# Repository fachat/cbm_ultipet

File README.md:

# Ulti-PET

Note: this is a part of a larger set of repositories, with [upet_family](https://github.com/fachat/upet_family) as the main repository.

This is a re-incarnation of the Commodore PET computer(s) from the later 1970s.

It is build on a PCB that fits into a C64-II case (with extra cutouts for connectors), and has only parts that can still be obtained new in 2024/2025.
A 3D-printed case is also available specific for the Ulti-PET PCB.

Videos on the machine are coming soon on the [YouTube 8-bit times](https://youtube.com/playlist?list=PLi1dzy7kw1iybjcUccgjCV4fhNH4IPWSx) channel.

## Features

The board is built with a number of features:

- Commodore 3032 / 4032 / 8032 / 8296 with options menu to select at boot
  - Boot-menu to select different PET versions to run (BASIC 1, 2, 4)
  - 40 and 80 col character display
  - 8296 memory map emulation
  - IEEE488 interface (card edge and 24pin flat ribbon cable)
  - Tape connector (card edge, incl. 9V for proper tape operation)
  - PET graphics keyboard, or alternatively a C64 keyboard
- Improved system design:
  - 512k video RAM, plus 512k fast RAM, accessible using banks on the W65816 CPU
  - boot from an SPI Flash ROM
  - up to 13.5 MHz mode (via configuration register)
  - Write protection for the PET ROMs once copied to RAM
  - lower 32k RAM mappable from all of the 512k fast RAM
  - single 5V power supply (<1A) using USB-C connector
  - hardware and firmware support SD-Card and USB keyboard or mouse
- Improved Audio output:
  - Original beeper sound
  - Audio output using a DAC with DMA
  - Dual SID output
  - beeper, DAC, and SID are mixed into a stereo line output
  - integrated amplifier can drive <1W speakers
- Improved Video output:
  - VGA colour video output (222 RGB)
  - up to 96x72 characters on screen
  - hires modes up to a 720x576 resolution
  - Dual 16 out of 64 colour palette, Colour-PET or C128 VDC-compatible, Sprites
  - Hires graphics mode (using a configuration register)
  - modifyable character set
  - multiple video pages mappable to $8000 video mem address
- Extra I/O features:
  - Userport Joystick, software-switchable between single and dual joystick configs
  - fast serial IEC for Commodore's 1581 or 1571 disk drives (ROM support TBD)
  - 5V SPI interface for further extensions
  - 3.3V SPI interface for further extensions
  - Adafruit(tm) UEXT interface for further extensions (SPI shared with 3.3V SPI, includes I2C)
  - Dual UART serial, one RS232, one TTL (shared with UEXT, or the USB-C-to-serial)

## Overview

The system architecture is actually rather simple, as you can see in the following graphics.

The main functionality is "hidden" inside the FPGA. It does:

1. clock generation and management
2. memory mapping
3. video generation.
4. SPI interface and boot
5. DAC DMA

On the CPU side of the FPGA it is actually a rather almost normal 65816 computer, 
with the exception that the bank register (that catches and stores the address lines 
A16-23 from the CPU's data bus) is in the FPGA, and that there is no ROM. The ROM has been
replaced with some code in the FPGA that copies the initial program to the CPU accessible
RAM, taking it from the Flash Boot ROM via SPI. This actually simplifies the design,
as 

1. parallel ROMs are getting harder to come by and
2. they are typically not as fast as is needed, and
3. with the SPI boot they don't occupy valuable CPU address space.

The video generation is done using time-sharing access to the video RAM.
The VGA output is 720x576 at 50Hz, or 720x480 at 60 Hz. So there is a pixel clock of 27MHz.

The system runs at 13.5MHz, so a byte of pixel output (i.e. eight pixels) has four
memory accesses to VRAM. Two of them are reserved for video access, one for fetching the
character data (e.g. at $08xxx in the PET), and the second one to fetch the "character ROM"
data, i.e. the pixel data for a character. This is also stored in VRAM, and is being loaded
there from the Flash Boot ROM by the initial boot loader.

The FPGA reads the character data, stores it to fetch the character pixel data, and streams
that out using its internal video shift register.

For more detailled descriptions of the features and how to use them, pls see the 
[FPGA repository](https://github.com/fachat/upet_fpga) that contains the code for the FPGA,
as described in the next section.

## I/O included in the Ulti-PET

The Ulti-PET not just has the Ultra-CPU, but also loads of I/O on the one board:

### Standard PET IO

The Ulti-PET includes the standard PET I/O features using the VIA and two PIAs, with some extensions. So, it has:

- IEEE488, including flat ribbon cable and card edge connector; with the additional capability of working as a device too
- Tape#1 (incl. 9V for proper tape operation), incl. card edge connector
- Tape#2 as TTL, but normally re-used for IEEE488 device handling
- PET keyboard, with the option to use a C64 keyboard, and the extended Ultipet-Keyboard
- PET userport, with the Video signal (optionally) replaced with 5V to accomodate user port extensions; incl. card edge connector
- Joystick connectors for the userport, software-switchable between single- or dual mode (compatible with 'stupid pet tricks')
- Reset and diag push buttons

### RS232

A Dual UART chip provides two serial interfaces. One interface is a real RS232 with a
DB9 connector. The other one is TTL level interface (shared with UEXT, see below).

The USB-C power connector has an USB-to-serial converter, that can be jumpered to the 
TTL level interface.

### Fast IEC

An IEC interface is provided using a second VIA chip. Using the VIA shift register, fast mode IEC
(like in the C128) is implemented.

### Dual SID and sound mixer

Two SID chips are included for your stereo sound pleasure.

The two SID outputs are mixed with the DAC audio output from the Ultra-CPU base.
Also, the beeper sound is mixed into the overall sound output.

Two audio amps are included to, so speakers can be directly connected to the board
(switched off when the audio jack is used).

### Keyboard shift lock and reset

When the shift-lock key in the replacement keyboard is defined on a specific position in 
the keyboard matrix (as is in the keyboard designed by Steve Gray), the key works like a shift-lock key.

In addition, pressing the shift-lock key longer (a few seconds), resets the machine 
(as long as the keyboard scanning still works).

### CS/A expansion board

The board has a full width CS/A slot for a single expansion card, plus a short CS/A board for
the accompanying [CS/A Ultrabus]() Ultra-Bus expansion board. This allows using (compatible)
Apple-II, RC2014, and C64 cartridges with the Ulti-PET.

(Older versions up to 1.2a had a problem there that is now fixed!)

### UEXT, and SPI-10 connectors

The board provides three standard I/O ports:

1. UEXT - this includes serial (see above), I2C, and SPI, all in 3.3V
2. SPI-10-3.3V - a 3.3V SPI interface for external modules (shared with UEXT)
3. SPI-10-5V - a 5V SPI interface provided by the second VIA, with selectable clock mode.

For the SPI-10 connectors see [here](http://forum.6502.org/viewtopic.php?f=4&t=4264&start=15#p48167).
For the UEXT connector see the Olimex [UEXT page](https://www.olimex.com/Products/Modules/UEXT/)

## Firmware features

Of the modern I/O, currently these are included and supported in the firmware, i.e. in the
BASIC4 models:

- USB keyboard or mouse support, if you select the boot option with a USB keyboard
- SD-Card support using the SD-Card filesystem from the Commander X16 provided by Michael Steil.
- C64 compatible kernal jump table

Note that if you select the boot option while holding the left shift key, a second optional 
configuration is being used.
For more details see the [ROM](https://github.com/fachat/upet_roms) repository, that contains
the current version of the firmware and accompanying documentation.
 
## Known Issues

The current revision is 1.3A

The known issues from the 1.2A version have been fixed.

A small number of non-functional issues has been found and documented. See the
[github list of issues](https://github.com/fachat/cbm_ultipet/issues?q=is%3Aissue%20state%3Aopen%20label%3Ar1.3a).

## Revision history

1.3a: Update:
- fixes for 1.2a known issues included, including improved audio mixer
- USB-C power supply connector, with USB-to-serial converter that can be connected to the internal 2nd serial port
- footprints for Joysticks improved and moved inwards
- footprint for VGA connector improved
- extended keyboard connector with I2C, and other lines
- extended pin header connectors for RS232
- improved pinout on FPGA to prep for HDMI (video output on differential pairs)
- optional pulldowns on audio out for original SIDs
- (most) THT parts have proper part numbers for JLCPCB for outsourced assembly too, not just SMD

1.2a: Update
- separate 3.3V generation for the bus, USB, and network, more bypass for SD cards
- Power, Shift Lock LED
- Remove 2nd oscillator option
- Digital video out connector for further experimentation
- Fix addressing of 2nd SID
- Replace some 1N4148 with 1N4448 for lower drop voltage, fix joystick diode direction
- Dual voltage divider for TTL beeper to avoid left/right audio crosstalk
- Fixes on the UART

1.1a: Update:
- Fixed userport joystick handling, allow software switching between single- and dual mode
- Include the beeper into the sound mixer
- Move from single UART to dual UART, to provide TTL serial or serial for UEXT
- Add I2C controller for UEXT
- Add UEXT, SPI-10-3.3V, SPI-10-5V connectors
- Add SPI interface with selectable modes on the second VIA (shares shift register with fast serial IEC bus)

1.0a: Initial release

## Building

Here are the subdirectories:

- [Board](Board/) that contains the board schematics and layout

Note that a case for the Ulti-PET is in the works - the case modifications for the Micro-PET do *not* work.

In addition, two other repositories are needed - they are separate as they are shared with other variants of the upet-family:

- [FPGA](https://github.com/fachat/upet_fpga) contains the VHDL code to program the FPGA logic chip used, and describes the configuration options - including the SPI usage, the DAC usage, and the Video features.
- [ROM](https://github.com/fachat/upet_roms) ROM contents to boot

### Board

To have the board built, you can use the gerbers that are stored in the zip file in the Board/production subdirectory.

To populate the board, there is an interactive bom (bill of materials) from KiCad, as well as the KiCad BOM CSV export in the [bom](Board/bom/) folder.

Parts numbers can be found in the [BOM list](Board/bom/cbm_ultipet_v1.2a-bom.xlsx). It has parts numbers for Mouser for all parts (except the SID), 
and for JLCPCB for the SMD parts. You can have JLCPCB assemble most of the SMD parts, and order the rest from Mouser. (Note, to not order parts twice, best
remove the JLPCB assembled parts before you upload to Mouser).

The BOM contains an Ethernet breakout board that is put into the connectors "above" the USB port. As an alternative you could use the 
[Wifi breakout board](https://github.com/fachat/upet_wifi). Note that at this time, this is not tested / programmed yet.

As an audio solution I am planning to use the Visaton K40SQ speakers, if you want to order them as well.

### FPGA

The FPGA is a Xilinx Spartan 6 programmable logic chip. It runs on 1.2V with 3.3V I/O and I programmed it in VHDL.

To build the FPGA content, clone the [FPGA](https://github.com/fachat/upet_fpga) repository, and look for the ultipetx.yz.bin, where the x.yz should be replaced with the current board
version, or the highest FPGA version below the board version.
This needs to be programmed into the SPI flash chip containing the configration for the FPGA.

To actually modify the code, you have to download and install the Xilinx WebISE software and open the ultipetx.yz.xise project file.

### ROM

To build the boot ROM image, clone the [ROM](https://github.com/fachat/upet_roms) repository, and build the spiimg70m file. This needs to be 
programmed into the SPI flash ROM containing the 65816 boot code.

The ROM image can be built using gcc, xa65, and make. Use your favourite EPROM programmer to burn it into the SPI Flash chip.

The ROM contains images of all required ROM images for BASIC 1, 2, and 4, and corresponding editor ROMs, including
some that have been extended with wedges.

The updated editor ROMs are from [Steve's Editor ROM project](http://www.6502.org/users/sjgray/projects/editrom/index.html) and can handle C64 keyboards, has a DOS wedge included, and resets into the Micro-PET boot menu.
For more details see the description in the ROM repository.

### Case

Currently no custom case is publicly available. I just didn't have time to build / test / write up the ones I have on tinkercad. Contact me privately and I can provide you a link.

## Gallery (R1.0)

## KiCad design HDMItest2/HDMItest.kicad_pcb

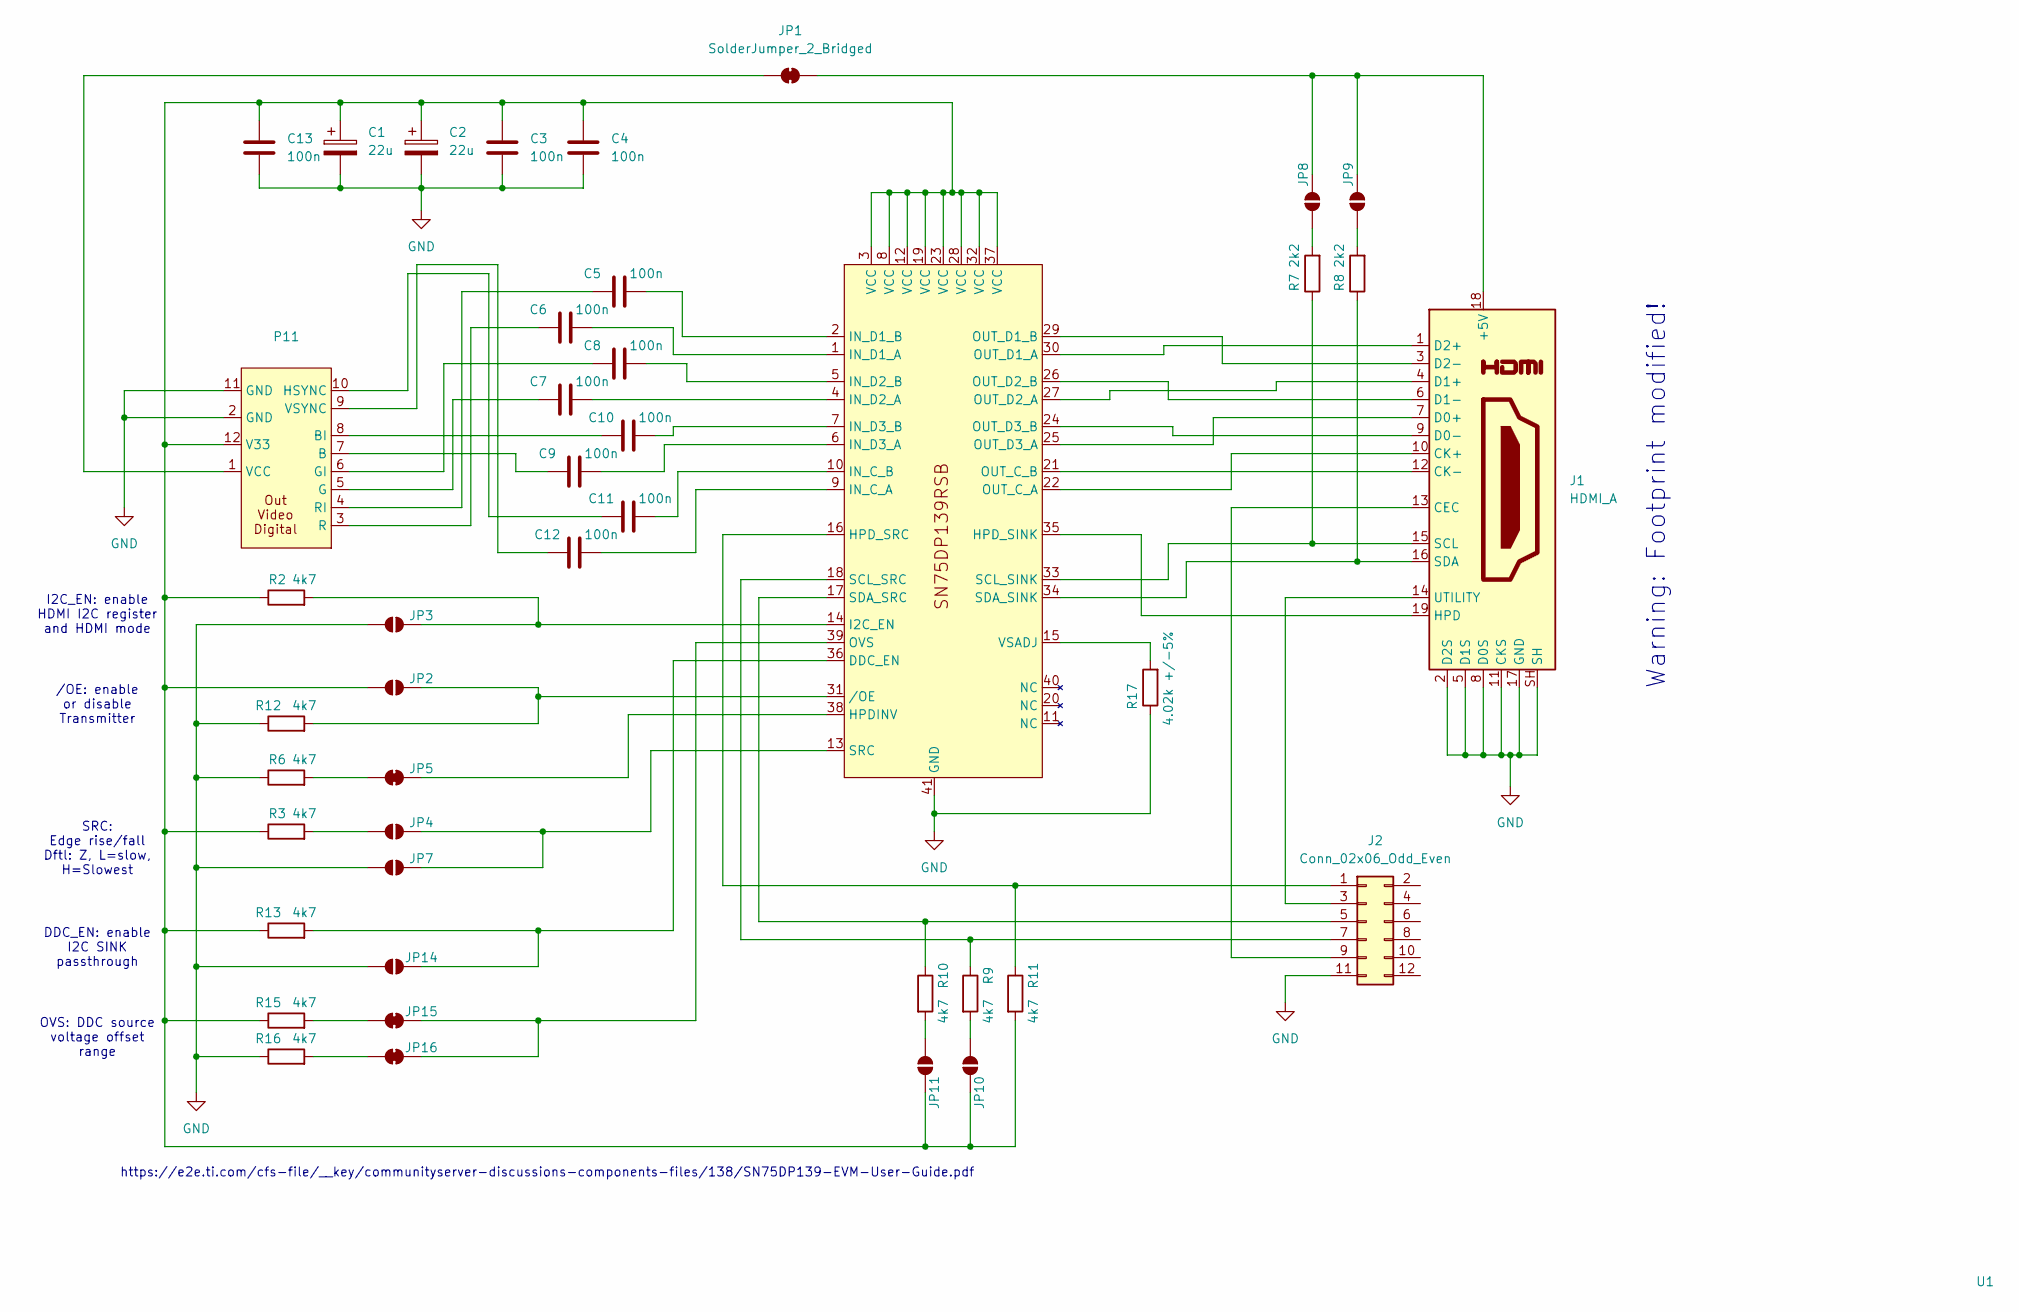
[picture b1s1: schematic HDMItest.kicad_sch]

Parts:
C1, C2: 22u; C_0805_2012Metric_Pad1.18x1.45mm_HandSolder; LCSC C45783
C3, C4, C5, C6, C7, C8, C9, C10, C11, C12, C13: 100n; C_0603_1608Metric_Pad1.08x0.95mm_HandSolder; LCSC C14663
J1: HDMI_A; HDMI_A_Molex_208658-1001_Horizontal; LCSC C138388
J2: Conn_02x06_Odd_Even; IDC-Header_2x06_P2.54mm_Vertical; LCSC C9136
JP1, JP5, JP15, JP16: SolderJumper_2_Bridged; SolderJumper-2_P1.3mm_Bridged_RoundedPad1.0x1.5mm
JP2, JP3, JP4, JP7, JP8, JP9, JP10, JP11, JP14: SolderJumper_2_Open; SolderJumper-2_P1.3mm_Open_RoundedPad1.0x1.5mm
P11: PinHeader_2x06_P2.54mm_Vertical
R2, R3, R6, R9, R10, R11, R12, R13, R15, R16: 4k7; R_0603_1608Metric_Pad0.98x0.95mm_HandSolder; LCSC C23162
R7, R8: 2k2; R_0603_1608Metric_Pad0.98x0.95mm_HandSolder; LCSC C22369817
R17: 4.02k +/-5%; R_0603_1608Metric_Pad0.98x0.95mm_HandSolder; LCSC C311906
U1: QFN-40-1EP_5x5mm_P0.4mm_EP3.8x3.8mm_ThermalVias; LCSC C2859698

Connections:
GND: C1.2, C2.2, C3.2, C4.2, C13.2, J1.2 (D2S), J1.5 (D1S), J1.8 (D0S), J1.11 (CKS), J1.17 (GND), J1.SH, J2.11, JP3.1 (A), JP7.1 (A), JP14.1 (A), P11.2 (GND), P11.11 (GND), R6.1, R12.1, R16.1, R17.1, U1.41 (GND)
unnamed: J1.18 (+5V), JP1.2 (B), JP8.2 (B), JP9.2 (B)
unnamed: J1.13 (CEC), J2.9
unnamed: J1.10 (CK+), U1.22 (OUT_C_A)
unnamed: J1.12 (CK-), U1.21 (OUT_C_B)
unnamed: J1.7 (D0+), U1.25 (OUT_D3_A)
unnamed: J1.9 (D0-), U1.24 (OUT_D3_B)
unnamed: J1.4 (D1+), U1.27 (OUT_D2_A)
unnamed: J1.6 (D1-), U1.26 (OUT_D2_B)
unnamed: J1.1 (D2+), U1.30 (OUT_D1_A)
unnamed: J1.3 (D2-), U1.29 (OUT_D1_B)
unnamed: J1.19 (HPD), U1.35 (HPD_SINK)
unnamed: J1.15 (SCL), R7.1, U1.33 (SCL_SINK)
unnamed: J1.16 (SDA), R8.1, U1.34 (SDA_SINK)
unnamed: J1.14 (UTILITY), J2.3
unnamed: J2.1, R11.1, U1.16 (HPD_SRC)
unnamed: J2.5, R10.1, U1.17 (SDA_SRC)
unnamed: J2.7, R9.1, U1.18 (SCL_SRC)
unnamed: JP1.1 (A), P11.1 (VCC)
unnamed: JP2.2 (B), R12.2, U1.31 (/OE)
unnamed: JP3.2 (B), R2.2, U1.14 (I2C_EN)
unnamed: JP4.1 (A), R3.2
unnamed: JP4.2 (B), JP7.2 (B), U1.13 (SRC)
unnamed: JP5.1 (A), R6.2
unnamed: JP5.2 (B), U1.38 (HPDINV)
unnamed: JP8.1 (A), R7.2
unnamed: JP9.1 (A), R8.2
unnamed: JP10.1 (A), R9.2
unnamed: C1.1, C2.1, C3.1, C4.1, C13.1, JP2.1 (A), JP10.2 (B), JP11.2 (B), P11.12 (V33), R2.1, R3.1, R11.2, R13.1, R15.1, U1.3 (VCC), U1.8 (VCC), U1.12 (VCC), U1.19 (VCC), U1.23 (VCC), U1.28 (VCC), U1.32 (VCC), U1.37 (VCC)
unnamed: JP11.1 (A), R10.2
unnamed: JP14.2 (B), R13.2, U1.36 (DDC_EN)
unnamed: JP15.1 (A), R15.2
unnamed: JP15.2 (B), JP16.2 (B), U1.39 (OVS)
unnamed: JP16.1 (A), R16.2
unnamed: C9.1, P11.7 (B)
unnamed: C10.1, P11.8 (BI)
unnamed: C7.1, P11.5 (G)
unnamed: C8.1, P11.6 (GI)
unnamed: C11.1, P11.10 (HSYNC)
unnamed: C6.1, P11.3 (R)
unnamed: C5.1, P11.4 (RI)
unnamed: C12.1, P11.9 (VSYNC)
unnamed: C12.2, U1.9 (IN_C_A)
unnamed: C11.2, U1.10 (IN_C_B)
unnamed: C6.2, U1.1 (IN_D1_A)
unnamed: C5.2, U1.2 (IN_D1_B)
unnamed: C7.2, U1.4 (IN_D2_A)
unnamed: C8.2, U1.5 (IN_D2_B)
unnamed: C9.2, U1.6 (IN_D3_A)
unnamed: C10.2, U1.7 (IN_D3_B)
unnamed: R17.2, U1.15 (VSADJ)

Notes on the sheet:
Warning: Footprint modified!
https://e2e.ti.com/cfs-file/__key/communityserver-discussions-components-files/138/SN75DP139-EVM-User-Guide.pdf
SRC: Edge rise/fall Dftl: Z, L=slow, H=Slowest
I2C_EN: enable HDMI I2C register and HDMI mode
/OE: enable or disable Transmitter
DDC_EN: enable I2C SINK passthrough
OVS: DDC source voltage offset range

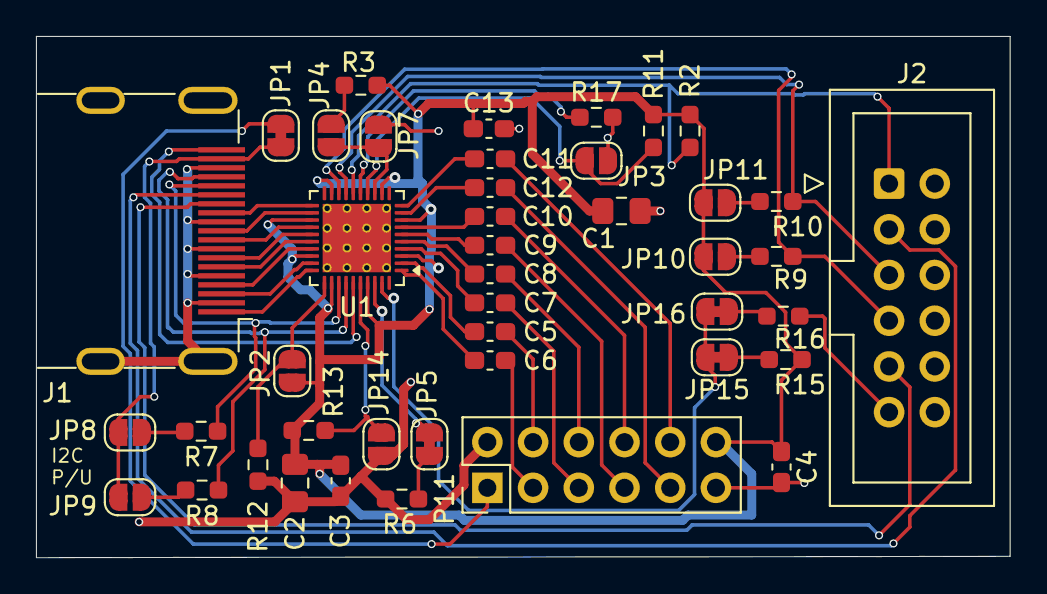
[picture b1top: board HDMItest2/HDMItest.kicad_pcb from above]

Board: 2 copper layers, 54.1 x 29.0 mm, 43 parts (0 on the bottom side), 51 nets.

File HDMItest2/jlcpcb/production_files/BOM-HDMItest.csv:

Comment,Designator,Footprint,LCSC,Quantity
100n,"C10,C11,C12,C13,C3,C4,C5,C6,C7,C8,C9",C_0603_1608Metric_Pad1.08x0.95mm_HandSolder,C14663,11
22u,"C1,C2",C_0805_2012Metric_Pad1.18x1.45mm_HandSolder,C45783,2
2k2,"R7,R8",R_0603_1608Metric_Pad0.98x0.95mm_HandSolder,C22369817,2
4.02k +/-5%,R17,R_0603_1608Metric_Pad0.98x0.95mm_HandSolder,C311906,1
4k7,"R10,R11,R12,R13,R15,R16,R2,R3,R6,R9",R_0603_1608Metric_Pad0.98x0.95mm_HandSolder,C23162,10
Conn_02x06_Odd_Even,J2,IDC-Header_2x06_P2.54mm_Vertical,C9136,1
HDMI_A,J1,HDMI_A_Molex_208658-1001_Horizontal,C138388,1
~,U1,QFN-40-1EP_5x5mm_P0.4mm_EP3.8x3.8mm_ThermalVias,C2859698,1

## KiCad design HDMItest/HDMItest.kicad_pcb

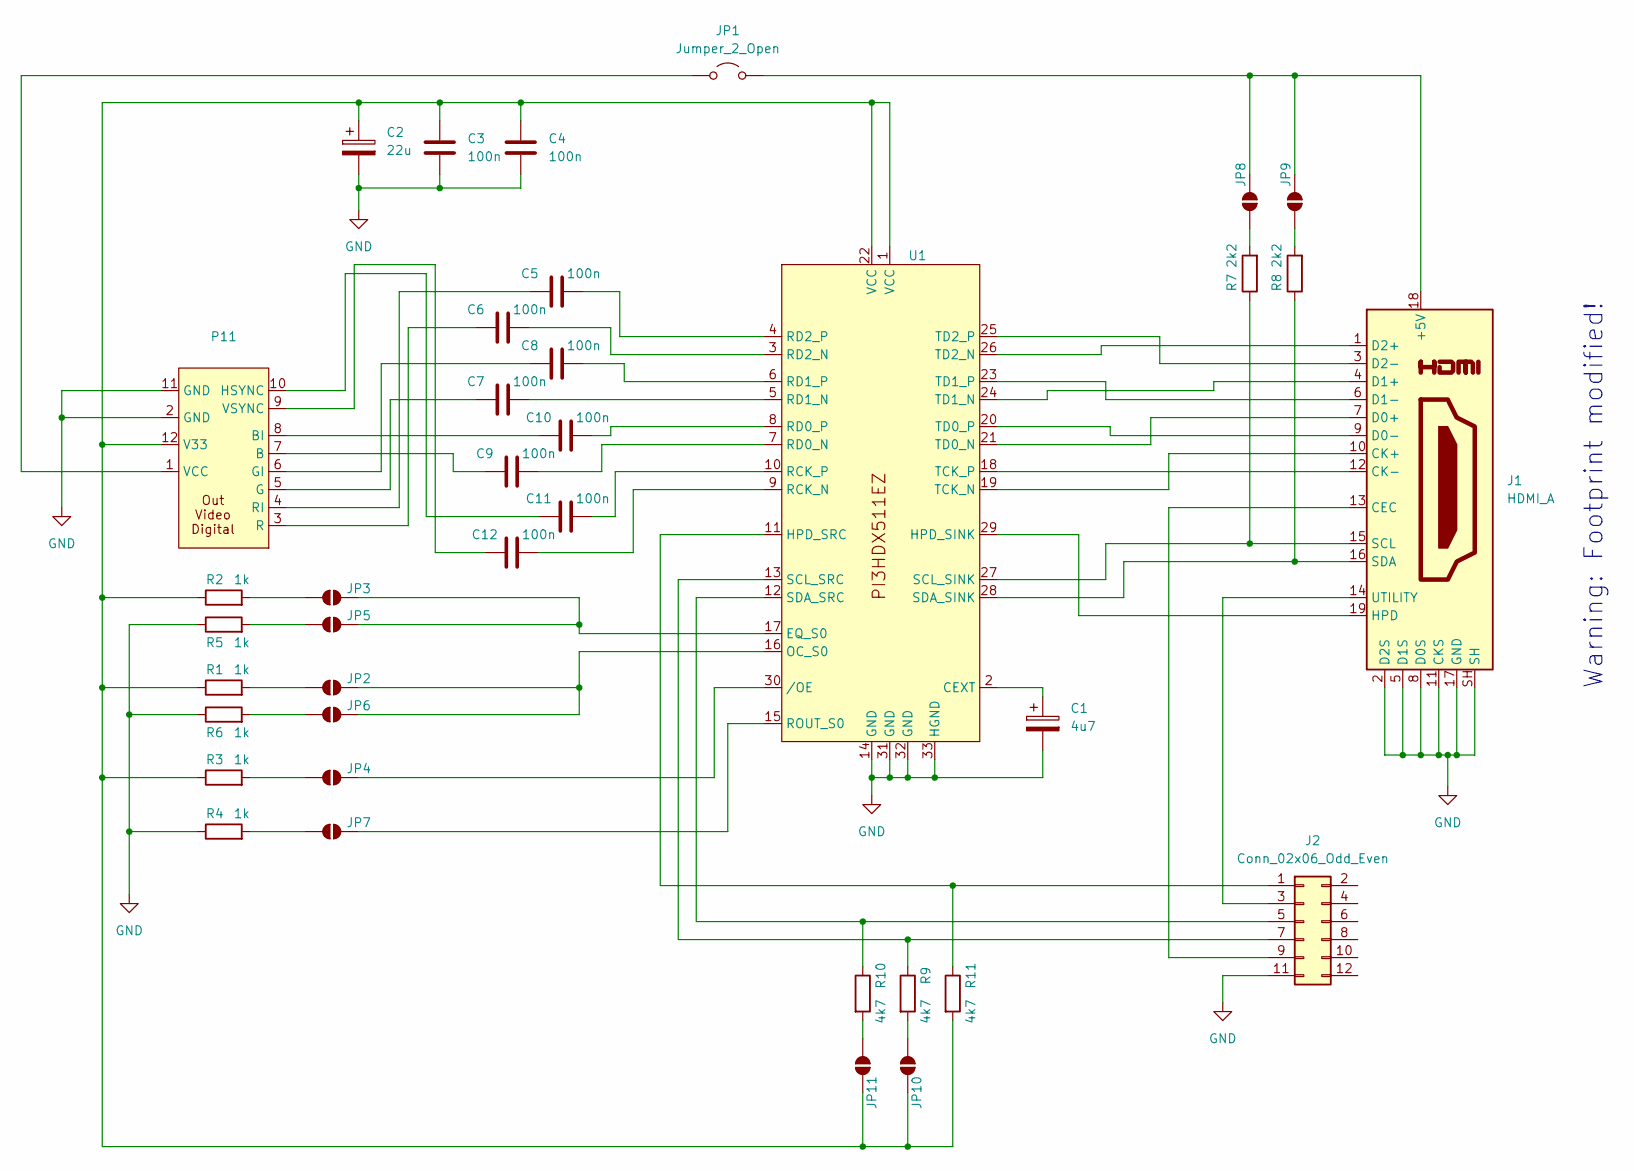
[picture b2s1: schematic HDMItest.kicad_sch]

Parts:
C1: 4u7; C_0805_2012Metric_Pad1.18x1.45mm_HandSolder; LCSC C1779
C2: 22u; C_0805_2012Metric_Pad1.18x1.45mm_HandSolder; LCSC C45783
C3, C4, C5, C6, C7, C8, C9, C10, C11, C12: 100n; C_0603_1608Metric_Pad1.08x0.95mm_HandSolder; LCSC C14663
J1: HDMI_A; HDMI_A_Molex_208658-1001_Horizontal; LCSC C138388
J2: Conn_02x06_Odd_Even; IDC-Header_2x06_P2.54mm_Vertical; LCSC C9136
JP1: Jumper_2_Open; PinHeader_1x02_P2.54mm_Vertical; LCSC C225477
JP2, JP3, JP4, JP5, JP6, JP7, JP8, JP9, JP10, JP11: SolderJumper_2_Open; SolderJumper-2_P1.3mm_Open_RoundedPad1.0x1.5mm
P11: PinHeader_2x06_P2.54mm_Vertical
R1, R2, R3, R4, R5, R6: 1k; R_0603_1608Metric_Pad0.98x0.95mm_HandSolder; LCSC C21190
R7, R8: 2k2; R_0603_1608Metric_Pad0.98x0.95mm_HandSolder; LCSC C22369817
R9, R10, R11: 4k7; R_0603_1608Metric_Pad0.98x0.95mm_HandSolder; LCSC C105428
U1: Diodes_ZL32_TQFN-32-1EP_3x6mm_P0.4mm_EP1.25x3.5mm; LCSC C2674182

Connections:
GND: C1.2, C2.2, C3.2, C4.2, J1.2 (D2S), J1.5 (D1S), J1.8 (D0S), J1.11 (CKS), J1.17 (GND), J1.SH, J2.11, P11.2 (GND), P11.11 (GND), R4.1, R5.1, R6.1, U1.14 (GND), U1.31 (GND), U1.32 (GND), U1.33 (HGND)
unnamed: J1.18 (+5V), JP1.2 (B), JP8.2 (B), JP9.2 (B)
unnamed: J1.13 (CEC), J2.9
unnamed: J1.10 (CK+), U1.19 (TCK_N)
unnamed: J1.12 (CK-), U1.18 (TCK_P)
unnamed: J1.7 (D0+), U1.21 (TD0_N)
unnamed: J1.9 (D0-), U1.20 (TD0_P)
unnamed: J1.4 (D1+), U1.24 (TD1_N)
unnamed: J1.6 (D1-), U1.23 (TD1_P)
unnamed: J1.1 (D2+), U1.26 (TD2_N)
unnamed: J1.3 (D2-), U1.25 (TD2_P)
unnamed: J1.19 (HPD), U1.29 (HPD_SINK)
unnamed: J1.15 (SCL), R7.1, U1.27 (SCL_SINK)
unnamed: J1.16 (SDA), R8.1, U1.28 (SDA_SINK)
unnamed: J1.14 (UTILITY), J2.3
unnamed: J2.1, R11.1, U1.11 (HPD_SRC)
unnamed: J2.5, R10.1, U1.12 (SDA_SRC)
unnamed: J2.7, R9.1, U1.13 (SCL_SRC)
unnamed: JP1.1 (A), P11.1 (VCC)
unnamed: JP2.1 (A), R1.2
unnamed: JP2.2 (B), JP6.2 (B), U1.16 (OC_S0)
unnamed: JP3.1 (A), R2.2
unnamed: JP3.2 (B), JP5.2 (B), U1.17 (EQ_S0)
unnamed: JP4.1 (A), R3.2
unnamed: JP4.2 (B), U1.30 (/OE)
unnamed: JP5.1 (A), R5.2
unnamed: JP6.1 (A), R6.2
unnamed: JP7.1 (A), R4.2
unnamed: JP7.2 (B), U1.15 (ROUT_S0)
unnamed: JP8.1 (A), R7.2
unnamed: JP9.1 (A), R8.2
unnamed: JP10.1 (A), R9.2
unnamed: C2.1, C3.1, C4.1, JP10.2 (B), JP11.2 (B), P11.12 (V33), R1.1, R2.1, R3.1, R11.2, U1.1 (VCC), U1.22 (VCC)
unnamed: JP11.1 (A), R10.2
unnamed: C9.1, P11.7 (B)
unnamed: C10.1, P11.8 (BI)
unnamed: C7.1, P11.5 (G)
unnamed: C8.1, P11.6 (GI)
unnamed: C11.1, P11.10 (HSYNC)
unnamed: C6.1, P11.3 (R)
unnamed: C5.1, P11.4 (RI)
unnamed: C12.1, P11.9 (VSYNC)
unnamed: C1.1, U1.2 (CEXT)
unnamed: C12.2, U1.9 (RCK_N)
unnamed: C11.2, U1.10 (RCK_P)
unnamed: C9.2, U1.7 (RD0_N)
unnamed: C10.2, U1.8 (RD0_P)
unnamed: C7.2, U1.5 (RD1_N)
unnamed: C8.2, U1.6 (RD1_P)
unnamed: C6.2, U1.3 (RD2_N)
unnamed: C5.2, U1.4 (RD2_P)

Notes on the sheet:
Warning: Footprint modified!

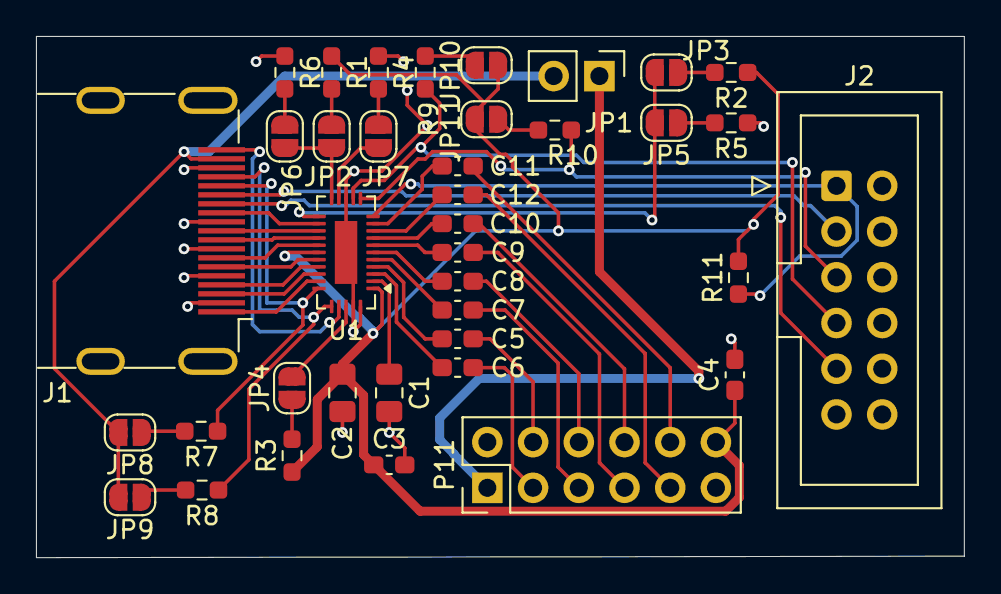
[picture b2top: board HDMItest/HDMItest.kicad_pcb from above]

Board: 2 copper layers, 51.5 x 29.0 mm, 38 parts (0 on the bottom side), 51 nets.

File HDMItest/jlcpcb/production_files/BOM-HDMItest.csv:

Comment,Designator,Footprint,LCSC,Quantity
100n,"C10,C11,C12,C3,C4,C5,C6,C7,C8,C9",C_0603_1608Metric_Pad1.08x0.95mm_HandSolder,C14663,10
1k,"R1,R2,R3,R4,R5,R6",R_0603_1608Metric_Pad0.98x0.95mm_HandSolder,C21190,6
22u,C2,C_0805_2012Metric_Pad1.18x1.45mm_HandSolder,C45783,1
2k2,"R7,R8",R_0603_1608Metric_Pad0.98x0.95mm_HandSolder,C22369817,2
4k7,"R10,R11,R9",R_0603_1608Metric_Pad0.98x0.95mm_HandSolder,C105428,3
4u7,C1,C_0805_2012Metric_Pad1.18x1.45mm_HandSolder,C1779,1
Conn_02x06_Odd_Even,J2,IDC-Header_2x06_P2.54mm_Vertical,C9136,1
HDMI_A,J1,HDMI_A_Molex_208658-1001_Horizontal,C138388,1
Jumper_2_Open,JP1,PinHeader_1x02_P2.54mm_Vertical,C225477,1
~,U1,Diodes_ZL32_TQFN-32-1EP_3x6mm_P0.4mm_EP1.25x3.5mm,C2674182,1

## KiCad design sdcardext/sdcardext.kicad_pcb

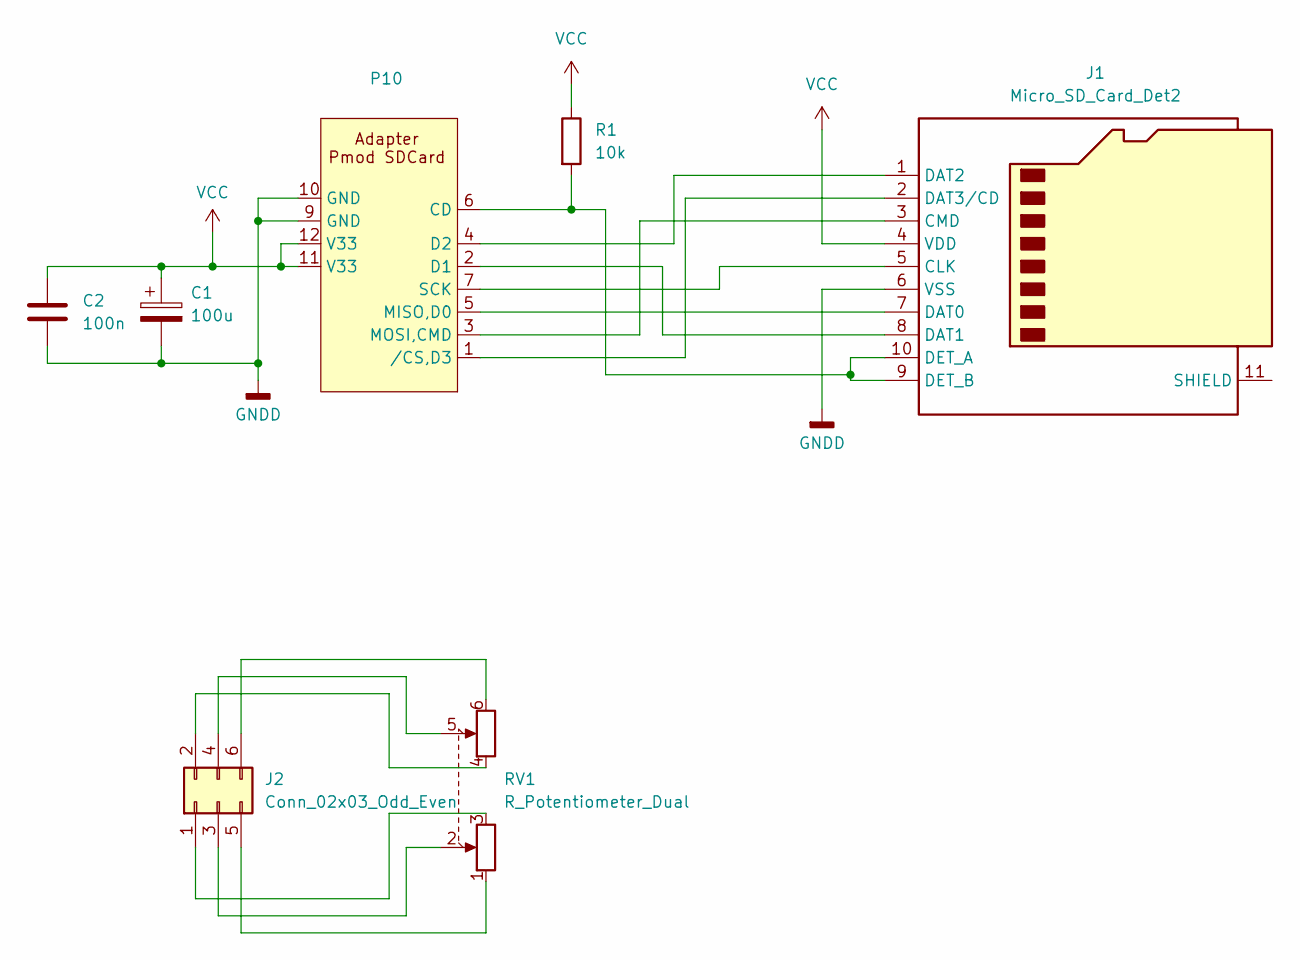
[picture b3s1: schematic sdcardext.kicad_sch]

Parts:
C1: 100u; C_1206_3216Metric_Pad1.33x1.80mm_HandSolder; LCSC C15008
C2: 100n; C_0603_1608Metric_Pad1.08x0.95mm_HandSolder; LCSC C14663
J1: Micro_SD_Card_Det2; microSD_HC_Molex_104031-0811; LCSC C585350
J2: Conn_02x03_Odd_Even; IDC-Header_2x03_P2.54mm_Horizontal; LCSC C34945
P10: IDC-Header_2x06_P2.54mm_Horizontal; LCSC C9141
R1: 10k; R_0603_1608Metric_Pad0.98x0.95mm_HandSolder; LCSC C25804
RV1: R_Potentiometer_Dual; Potentiometer_Alps_RK097_Dual_Horizontal_Switch; LCSC C336003

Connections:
GNDD: C1.2, C2.2, J1.6 (VSS), P10.9 (GND), P10.10 (GND)
unnamed: J1.5 (CLK), P10.7 (SCK)
unnamed: J1.3 (CMD), P10.3 (MOSI,CMD)
unnamed: J1.7 (DAT0), P10.5 (MISO,D0)
unnamed: J1.8 (DAT1), P10.2 (D1)
unnamed: J1.1 (DAT2), P10.4 (D2)
unnamed: J1.2 (DAT3/CD), P10.1 (/CS,D3)
unnamed: J1.9 (DET_B), J1.10 (DET_A), P10.6 (CD), R1.2
unnamed: J2.1, RV1.3
unnamed: J2.2, RV1.4
unnamed: J2.3, RV1.2
unnamed: J2.4, RV1.5
unnamed: J2.5, RV1.1
unnamed: J2.6, RV1.6
VCC: C1.1, C2.1, J1.4 (VDD), P10.11 (V33), P10.12 (V33), R1.1

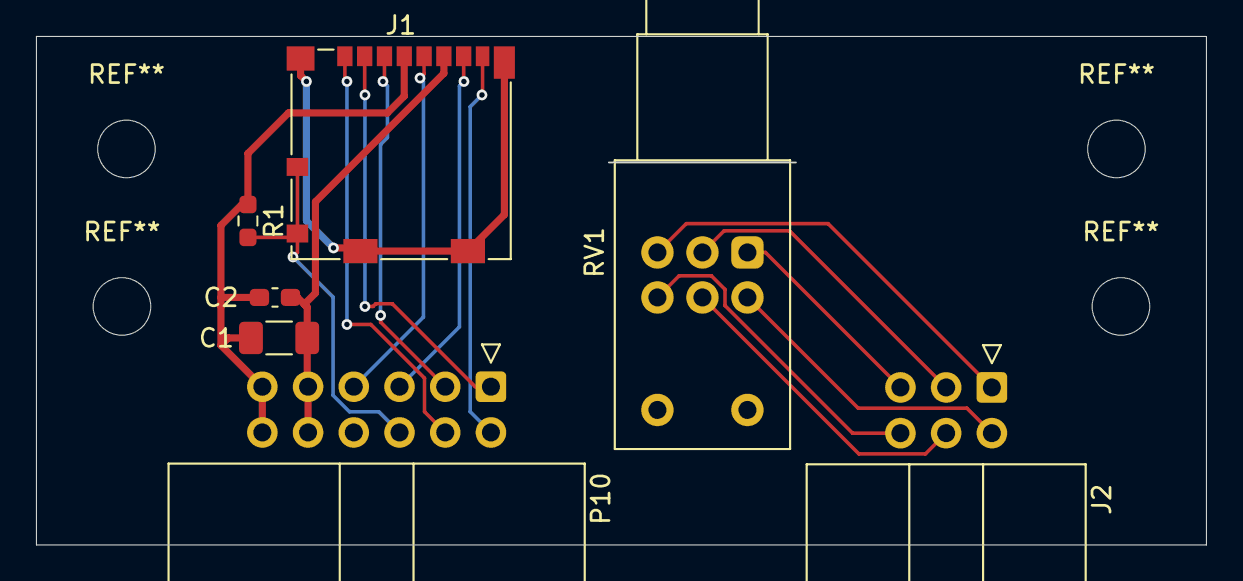
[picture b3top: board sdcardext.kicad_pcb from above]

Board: 2 copper layers, 65.0 x 28.2 mm, 7 parts (0 on the bottom side), 15 nets.

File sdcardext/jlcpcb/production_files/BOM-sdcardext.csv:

Comment,Designator,Footprint,LCSC,Quantity
100n,C2,C_0603_1608Metric_Pad1.08x0.95mm_HandSolder,C14663,1
100u,C1,C_1206_3216Metric_Pad1.33x1.80mm_HandSolder,C15008,1
10k,R1,R_0603_1608Metric_Pad0.98x0.95mm_HandSolder,C25804,1
Conn_02x03_Odd_Even,J2,IDC-Header_2x03_P2.54mm_Horizontal,C34945,1
Micro_SD_Card_Det2,J1,microSD_HC_Molex_104031-0811,C585350,1
R_Potentiometer_Dual,RV1,Potentiometer_Alps_RK097_Dual_Horizontal_Switch,C336003,1
~,P10,IDC-Header_2x06_P2.54mm_Horizontal,C9141,1

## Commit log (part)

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2024-02-03 initial publish
2024-02-03 fix a trace width
2024-04-03 Ultipet 1.0A final
2024-06-19 publish ultipet 1.0a
2024-06-19 ultipet 1.1a board
2024-06-19 update system arch diagram
2024-06-20 add link to family repo
2024-06-26 handle (no) sub repos
2024-10-10 update SID footprints - still conflicting
2024-10-10 diverse fixes
2024-10-13 various fixes as documented in github issues
2024-10-14 more fixes
2024-10-17 clamp diodes for joysticks
2024-10-19 new placement for 1.2a
2024-10-20 layout work
2024-10-22 more layout work
2024-11-15 generic add digital video out connector
2024-11-17 improve mixer, reduce noise
2024-11-17 add bypass caps for SD Cards
2024-11-17 add gerbers for 1.2a
2024-11-24 replace some ultipet specific TQFP with easier to solder parts
2024-11-25 as ordered for 3rd prototype
2024-11-28 updated bom
2024-11-28 cleanup bom files
2024-11-28 separate mouser BOM with zero qty lines removed
2024-12-01 add reverser board for expansion bus
2024-12-01 add note regarding reverser board
2024-12-02 add oscillator fix board
2025-01-05 bom redo
2025-01-13 add known bugs and fixes for 1.2a
2025-01-13 more on fixes
2025-01-13 fix boms, audio connector footprint
2025-01-15 clarified fixes
2025-01-19 more clarification on fix pictures
2025-01-26 update bom
2025-01-26 fixed power switch footprint that got replaced on some update
2025-01-26 first work on r1.3
2025-01-26 more work on 1.3
2025-05-12 add Warning about kicad 9
2025-05-24 add pdf schematics
2025-05-24 add schematics pdf
2025-08-05 work on 1.3
2025-08-06 work on r1.3
2025-08-06 more work on r1.3
2025-08-06 preview for r1.3
2025-08-06 add missing chg log for mixer
2025-08-06 layout work on r1.3a
2025-08-07 more layout work on r1.3
2025-08-07 fix DS1818 layout
2025-08-09 stash
2025-08-09 add some jumper options, layout work
2025-08-09 fix pcb outline
2025-08-10 new USB C conn; BOM work
2025-08-10 more work on BOM
2025-08-10 rename U refs to UX*
2025-08-10 working on jlcpcb production files
2025-08-11 cleanup folder
2025-08-11 some layout fixes, more parts
2025-08-11 update schem pdf and production files
2025-08-28 small changes
2025-08-28 add some footprints
2025-08-28 add test boards
2026-02-22 adding SID mirroring to schem
2026-03-12 add sdcard breakout
2026-03-12 add part#, pullup for CD
2026-03-15 SD card and volumn poti test extension
2026-05-08 add C64 restore
